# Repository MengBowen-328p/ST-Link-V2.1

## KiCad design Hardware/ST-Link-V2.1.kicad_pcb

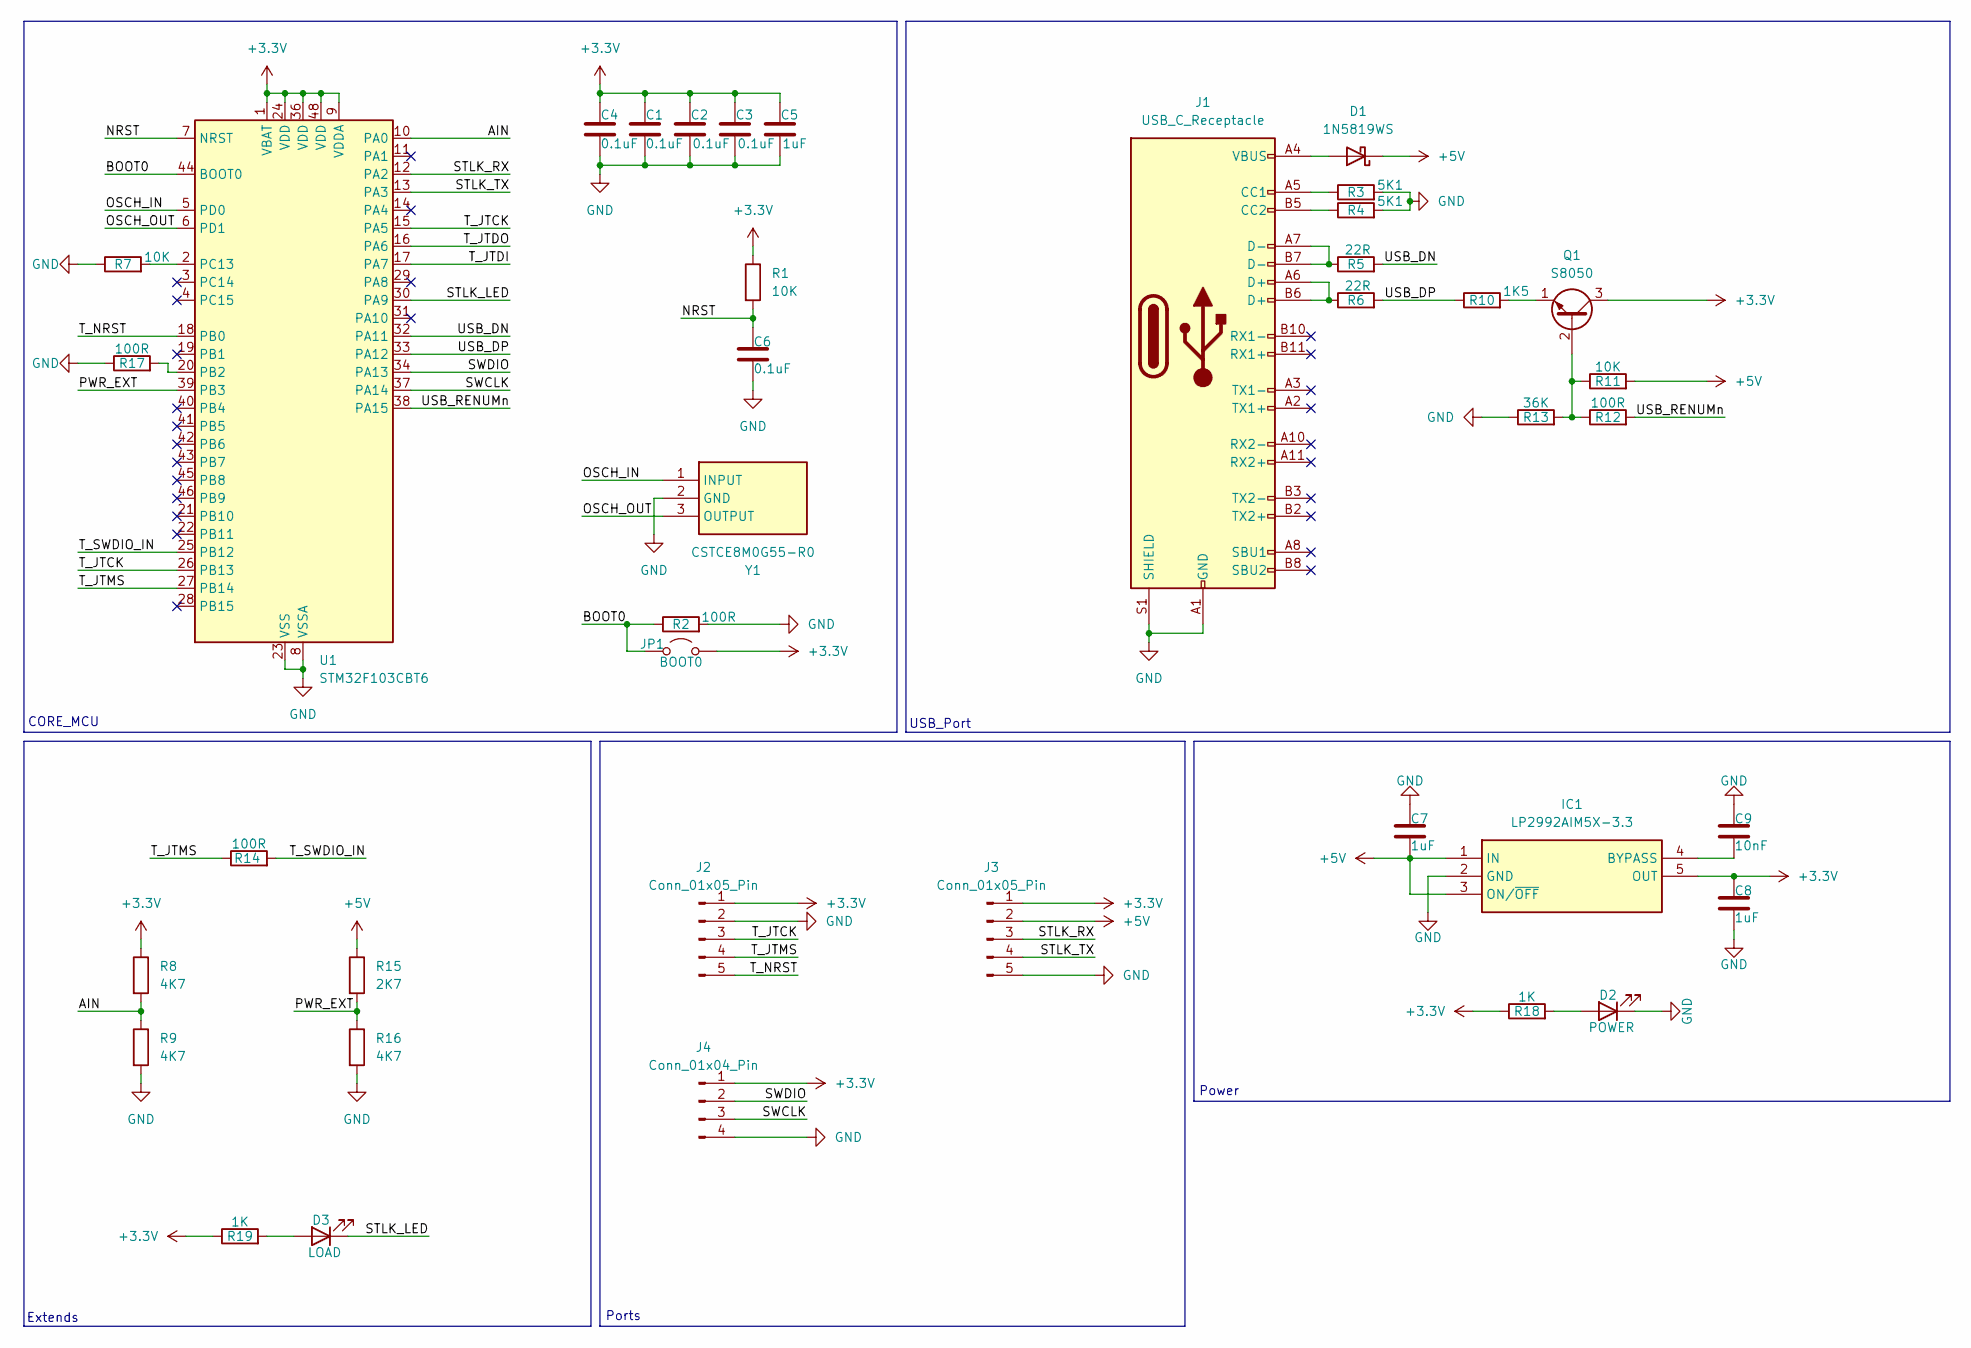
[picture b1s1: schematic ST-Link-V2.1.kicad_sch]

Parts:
C1, C2, C3, C4, C6: 0.1uF; C_0603_1608Metric
C5, C7, C8: 1uF; C_0603_1608Metric
C9: 10nF; C_0603_1608Metric
D1: 1N5819WS; D_SOD-323
D2: POWER; LED_0603_1608Metric
D3: LOAD; LED_0603_1608Metric
IC1: LP2992AIM5X-3.3; SOT95P280X145-5N; Manufacturer_Part_Number LP2992AIM5X-3.3; Mouser Part Number 926-LP2992AIM5X-33
J1: USB_C_Receptacle; USB_C_Receptacle_XKB_U262-16XN-4BVC11
J2, J3: Conn_01x05_Pin; STLINK_PIN
J4: Conn_01x04_Pin; SWD_Port
JP1: BOOT0; SolderJumper-2_P1.3mm_Open_RoundedPad1.0x1.5mm
Q1: S8050; SOT-23-3
R1, R7, R11: 10K; R_0603_1608Metric
R2, R12, R14, R17: 100R; R_0603_1608Metric
R3, R4: 5K1; R_0603_1608Metric
R5, R6: 22R; R_0603_1608Metric
R8, R9, R16: 4K7; R_0603_1608Metric
R10: 1K5; R_0603_1608Metric
R13: 36K; R_0603_1608Metric
R15: 2K7; R_0603_1608Metric
R18, R19: 1K; R_0603_1608Metric
U1: STM32F103CBT6; LQFP-48_7x7mm_P0.5mm
Y1: CSTCE8M0G55-R0; CSTCE12M0G55R0; Manufacturer_Part_Number CSTCE12M0G55-R0; Mouser Part Number 81-CSTCE12M0G55-R0

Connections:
+3.3V: C1.1, C2.1, C3.1, C4.1, C5.1, C8.1, IC1.5 (OUT), J2.1, J3.1, J4.1, JP1.2 (B), Q1.3 (C), R1.1, R8.1, R18.1, R19.1, U1.1 (VBAT), U1.9 (VDDA), U1.24 (VDD), U1.36 (VDD), U1.48 (VDD)
+5V: C7.2, D1.1 (K), IC1.1 (IN), IC1.3 (ON/~OFF), J3.2, R11.2, R15.1
/AIN: R8.2, R9.1, U1.10 (PA0)
/BOOT0: JP1.1 (A), R2.1, U1.44 (BOOT0)
/NRST: C6.1, R1.2, U1.7 (NRST)
/OSCH_IN: U1.5 (PD0), Y1.1 (INPUT)
/OSCH_OUT: U1.6 (PD1), Y1.3 (OUTPUT)
/PWR_EXT: R15.2, R16.1, U1.39 (PB3)
/STLK_LED: D3.1 (K), U1.30 (PA9)
/STLK_RX: J3.3, U1.12 (PA2)
/STLK_TX: J3.4, U1.13 (PA3)
/SWCLK: J4.3, U1.37 (PA14)
/SWDIO: J4.2, U1.34 (PA13)
/T_JTCK: J2.3, U1.15 (PA5), U1.26 (PB13)
/T_JTDI: U1.17 (PA7)
/T_JTDO: U1.16 (PA6)
/T_JTMS: J2.4, R14.1, U1.27 (PB14)
/T_NRST: J2.5, U1.18 (PB0)
/T_SWDIO_IN: R14.2, U1.25 (PB12)
/USB_DN: R5.2, U1.32 (PA11)
/USB_DP: R6.2, R10.1, U1.33 (PA12)
/USB_RENUMn: R12.2, U1.38 (PA15)
GND: C1.2, C2.2, C3.2, C4.2, C5.2, C6.2, C7.1, C8.2, C9.1, D2.1 (K), IC1.2 (GND), J1.A1 (GND), J1.A12 (GND), J1.B1 (GND), J1.B12 (GND), J1.S1 (SHIELD), J2.2, J3.5, J4.4, R2.2, R3.2, R4.2, R7.1, R9.2, R13.1, R16.2, R17.1, U1.8 (VSSA), U1.23 (VSS), U1.35 (VSS), U1.47 (VSS), Y1.2 (GND)
unnamed: D1.2 (A), J1.A4 (VBUS), J1.A9 (VBUS), J1.B4 (VBUS), J1.B9 (VBUS)
unnamed: D2.2 (A), R18.2
unnamed: D3.2 (A), R19.2
unnamed: C9.2, IC1.4 (BYPASS)
unnamed: J1.A5 (CC1), R3.1
unnamed: J1.B5 (CC2), R4.1
unnamed: J1.A6 (D+), J1.B6 (D+), R6.1
unnamed: J1.A7 (D-), J1.B7 (D-), R5.1
unnamed: Q1.2 (B), R11.1, R12.1, R13.2
unnamed: Q1.1 (E), R10.2
unnamed: R17.2, U1.20 (PB2)
unnamed: R7.2, U1.2 (PC13)

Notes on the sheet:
CORE_MCU
USB_Port
Ports
Extends
Power

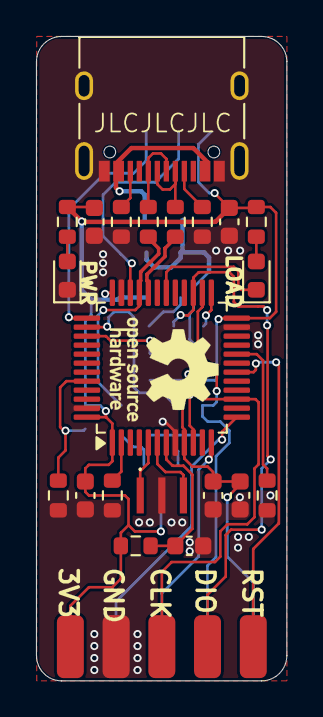
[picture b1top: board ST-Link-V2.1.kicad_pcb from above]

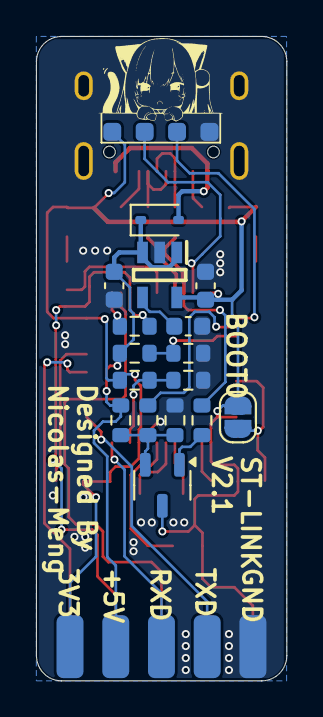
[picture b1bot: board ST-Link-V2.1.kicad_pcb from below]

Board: 2 copper layers, 13.9 x 35.8 mm, 40 parts (18 on the bottom side), 33 nets.

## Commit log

2024-10-06 Update Hardware
